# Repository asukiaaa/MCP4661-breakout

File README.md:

# MCP4661-breakout

A breakout board to use MCP4641 designed with using KiCad.

https://www.digikey.jp/ja/products/detail/microchip-technology/MCP4661T-103E-ML/2059724

## Compatible library for Arduino

[MCP4661_asukiaaa](https://github.com/asukiaaa/arduino-MCP4661)

## License

MIT

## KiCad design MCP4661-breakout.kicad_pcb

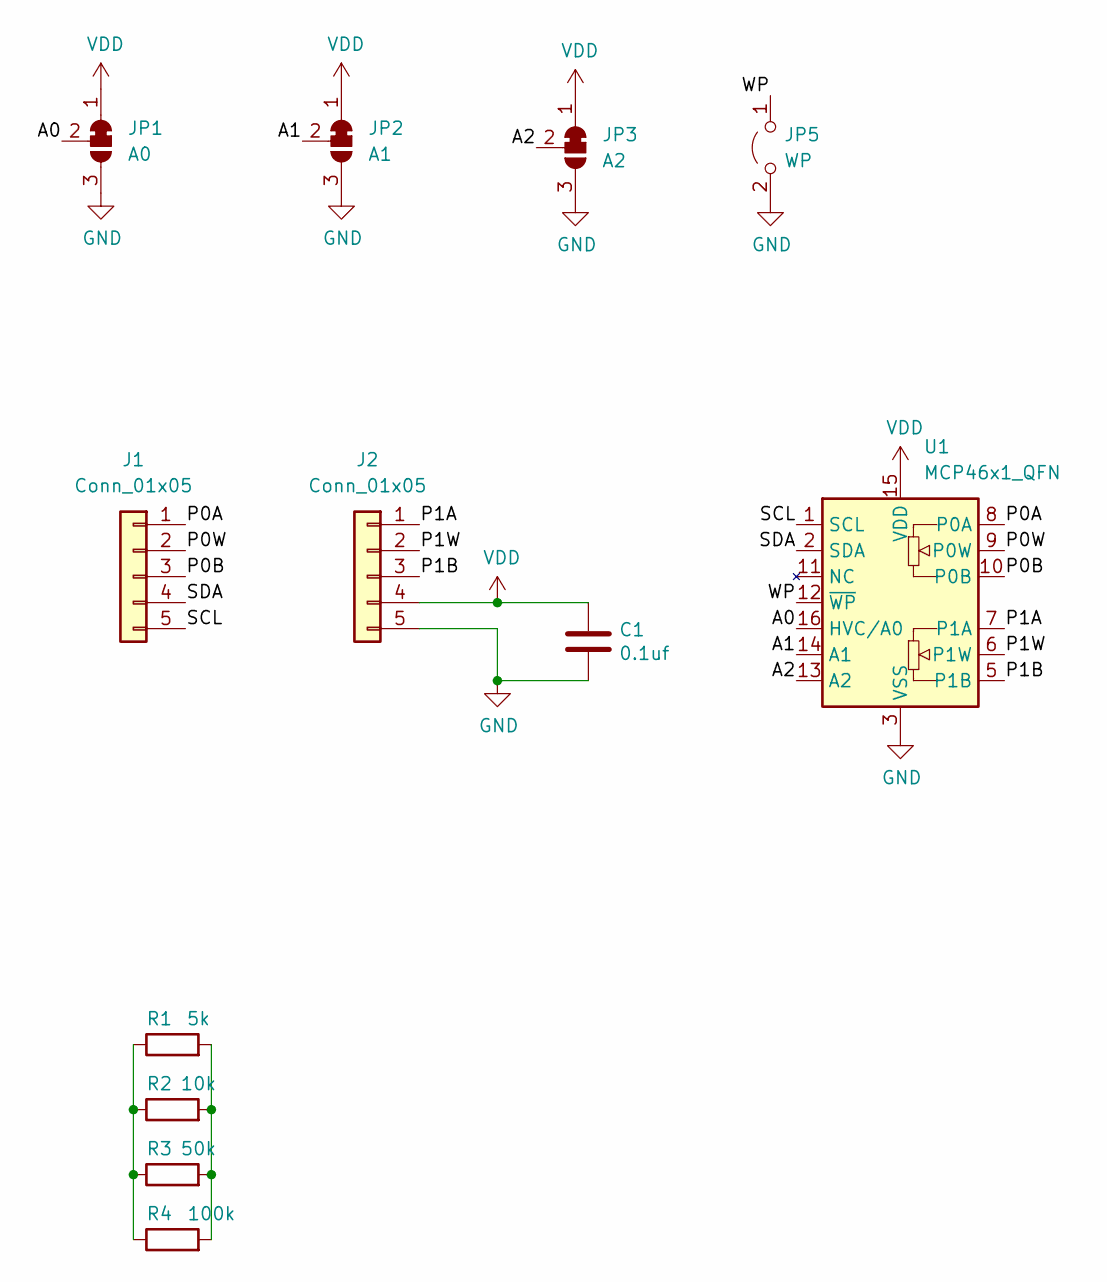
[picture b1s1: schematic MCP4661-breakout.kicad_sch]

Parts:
C1: 0.1uf; C_0402_1005Metric
J1: Conn_01x05; PinHeader_1x05_P2.54mm_Vertical_without_lines
J2: Conn_01x05; PinHeader_1x05_P2.54mm_Vertical_without_lines_all_circles
JP1: A0; SolderJumper-3_P1.3mm_Bridged12_Pad1.0x1.5mm_without_1pad_m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
JP2: A1; SolderJumper-3_P1.3mm_Bridged12_Pad1.0x1.5mm_without_1pad_m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
JP3: A2; SolderJumper-3_P1.3mm_Bridged12_Pad1.0x1.5mm_without_1pad_m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
JP5: WP; SolderJumper-2_P1.3mm_Open_Pad1.0x1.5mm
R1: 5k; R_0402_1005Metric
R2: 10k; R_0402_1005Metric
R3: 50k; R_0402_1005Metric
R4: 100k; R_0402_1005Metric
U1: MCP46x1_QFN; QFN-16-1EP_4x4mm_P0.65mm_EP2.5x2.5mm

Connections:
/A0: JP1.2 (C), U1.16 (HVC/A0)
/A1: JP2.2 (C), U1.14 (A1)
/A2: JP3.2 (C), U1.13 (A2)
/P0A: J1.1, U1.8 (P0A)
/P0B: J1.3, U1.10 (P0B)
/P0W: J1.2, U1.9 (P0W)
/P1A: J2.1, U1.7 (P1A)
/P1B: J2.3, U1.5 (P1B)
/P1W: J2.2, U1.6 (P1W)
/SCL: J1.5, U1.1 (SCL)
/SDA: J1.4, U1.2 (SDA)
/WP: JP5.1 (A), U1.12 (~WP)
GND: C1.2, J2.5, JP1.3 (B), JP2.3 (B), JP3.3 (B), JP5.2 (B), U1.3 (VSS), U1.4 (VSS), U1.17 (EP)
unnamed: R1.1, R2.1, R3.1, R4.1
unnamed: R1.2, R2.2, R3.2, R4.2
VDD: C1.1, J2.4, JP1.1 (A), JP2.1 (A), JP3.1 (A), U1.15 (VDD)

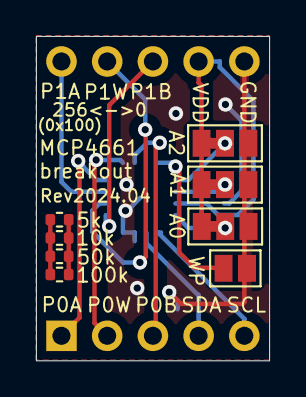
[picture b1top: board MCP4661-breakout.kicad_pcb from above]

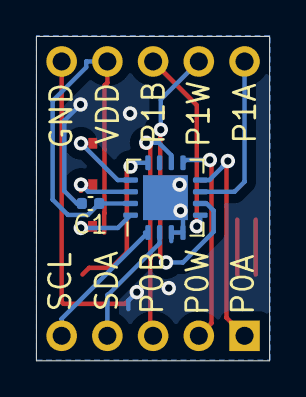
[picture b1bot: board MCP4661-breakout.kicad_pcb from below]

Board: 2 copper layers, 13.0 x 18.0 mm, 12 parts (4 on the bottom side), 16 nets.

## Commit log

2024-03-14 Add bom files for each resistor types
2024-05-26 Change font thicker
2024-05-26 Add library info for Arduino
2024-05-26 Add pdf file of schema
